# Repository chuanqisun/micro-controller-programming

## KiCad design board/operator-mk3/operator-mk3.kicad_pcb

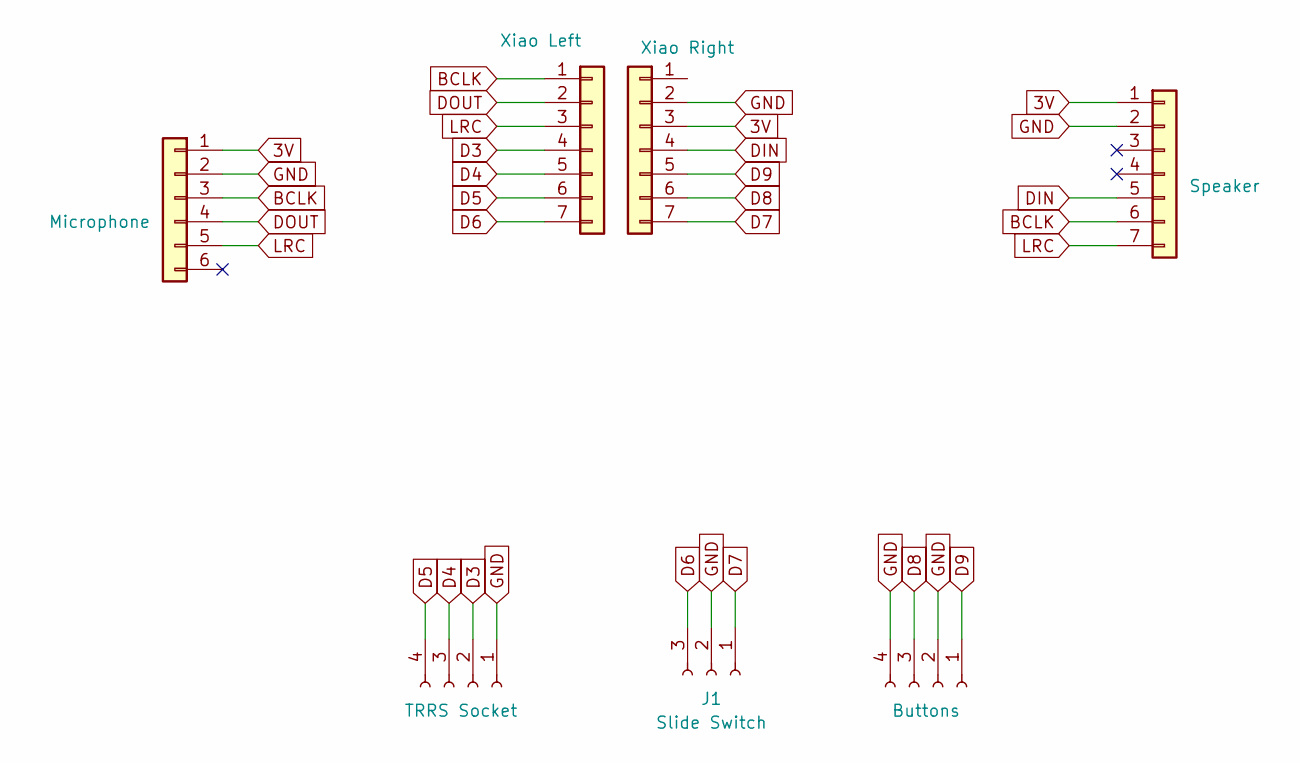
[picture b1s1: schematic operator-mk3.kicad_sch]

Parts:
J1: Slide Switch; PinSocket_1x03_P2.54mm_Vertical
J2: Microphone; PinSocket_1x06_P2.54mm_Vertical
J3: Buttons; PinSocket_1x04_P2.54mm_Vertical
J4: Speaker; PinSocket_1x07_P2.54mm_Vertical
J5: Xiao Left; PinSocket_1x07_P2.54mm_Vertical
J6: Xiao Right; PinSocket_1x07_P2.54mm_Vertical
J8: TRRS Socket; PinSocket_1x04_P2.54mm_Vertical

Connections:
3V: J2.1, J4.1, J6.3
BCLK: J2.3, J4.6, J5.1
D3: J5.4, J8.2
D4: J5.5, J8.3
D5: J5.6, J8.4
D6: J1.3, J5.7
D7: J1.1, J6.7
D8: J3.3, J6.6
D9: J3.1, J6.5
DIN: J4.5, J6.4
DOUT: J2.4, J5.2
GND: J1.2, J2.2, J3.2, J3.4, J4.2, J6.2, J8.1
LRC: J2.5, J4.7, J5.3

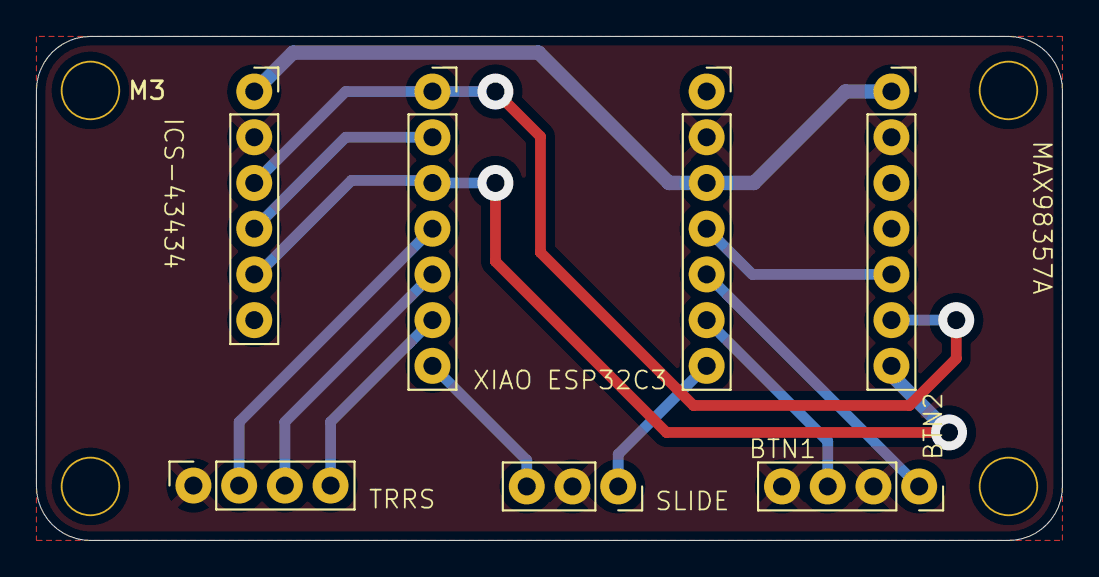
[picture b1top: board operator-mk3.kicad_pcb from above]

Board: 2 copper layers, 57.0 x 28.0 mm, 7 parts (0 on the bottom side), 13 nets.

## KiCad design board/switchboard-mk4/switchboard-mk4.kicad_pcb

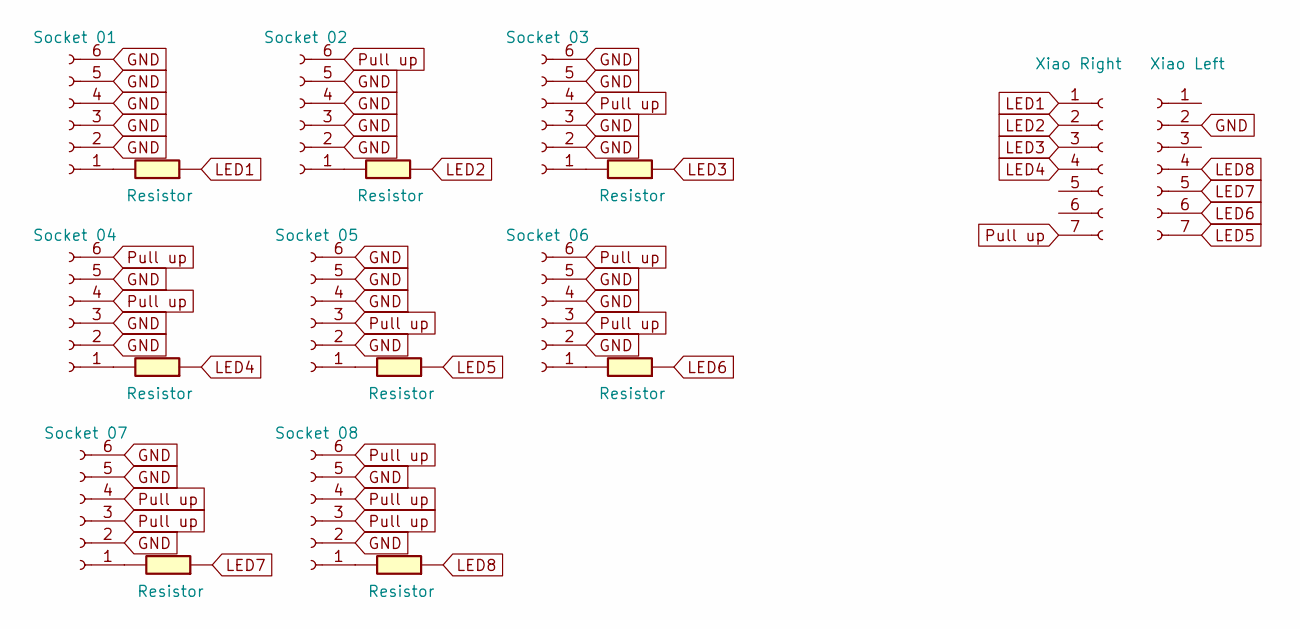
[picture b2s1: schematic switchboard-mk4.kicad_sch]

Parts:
J1: Socket 02; PinSocket_1x06_P2.54mm_Vertical
J2: Socket 03; PinSocket_1x06_P2.54mm_Vertical
J3: Socket 01; PinSocket_1x06_P2.54mm_Vertical
J4: Socket 06; PinSocket_1x06_P2.54mm_Vertical
J5: Socket 05; PinSocket_1x06_P2.54mm_Vertical
J6: Socket 04; PinSocket_1x06_P2.54mm_Vertical
J7: Socket 07; PinSocket_1x06_P2.54mm_Vertical
J8: Socket 08; PinSocket_1x06_P2.54mm_Vertical
J9: Xiao Right; PinSocket_1x07_P2.54mm_Vertical
J10: Xiao Left; PinSocket_1x07_P2.54mm_Vertical
R1, R2, R7, R8, R9, R10, R11, R12: Resistor; R_1206

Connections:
GND: J1.2, J1.3, J1.4, J1.5, J2.2, J2.3, J2.5, J2.6, J3.2, J3.3, J3.4, J3.5, J3.6, J4.2, J4.4, J4.5, J5.2, J5.4, J5.5, J5.6, J6.2, J6.3, J6.5, J7.2, J7.5, J7.6, J8.2, J8.5, J10.2
LED1: J9.1, R8.2
LED2: J9.2, R7.2
LED3: J9.3, R2.2
LED4: J9.4, R1.2
LED5: J10.7, R9.2
LED6: J10.6, R10.2
LED7: J10.5, R11.2
LED8: J10.4, R12.2
unnamed: J1.1, R7.1
unnamed: J2.1, R2.1
unnamed: J3.1, R8.1
unnamed: J4.1, R10.1
unnamed: J5.1, R9.1
unnamed: J6.1, R1.1
unnamed: J7.1, R11.1
unnamed: J8.1, R12.1
Pull up: J1.6, J2.4, J4.3, J4.6, J5.3, J6.4, J6.6, J7.3, J7.4, J8.3, J8.4, J8.6, J9.7

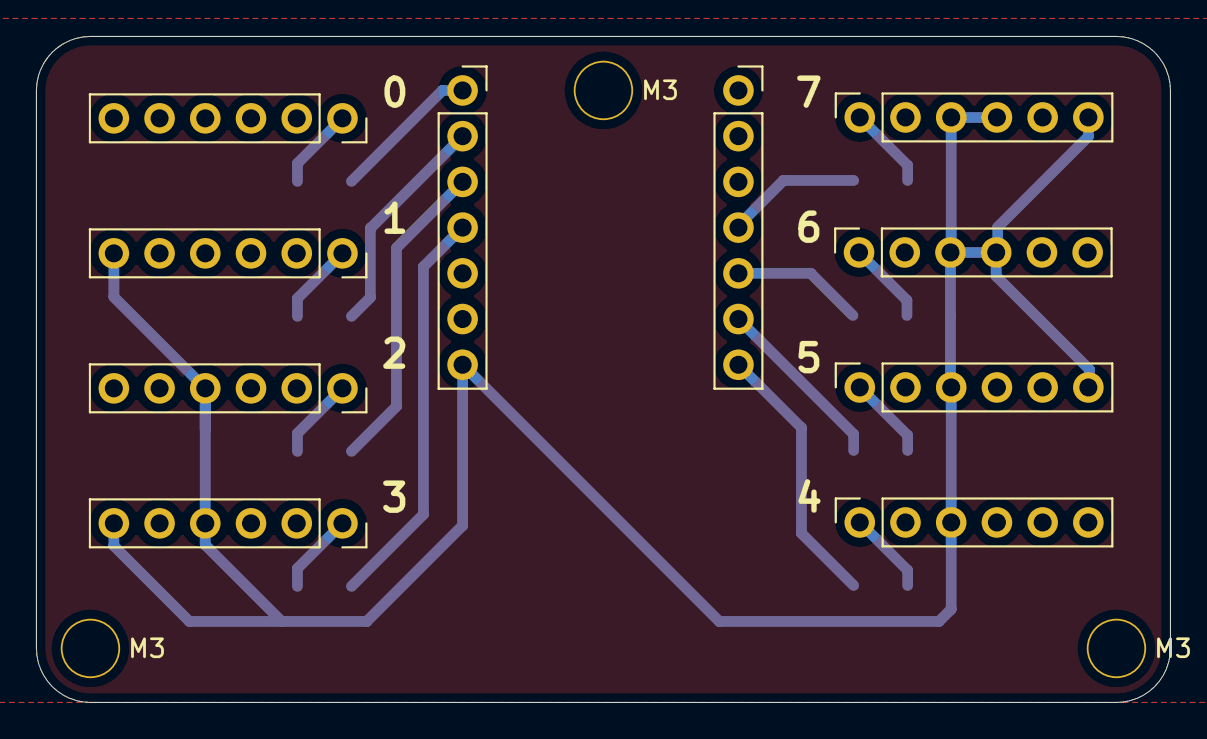
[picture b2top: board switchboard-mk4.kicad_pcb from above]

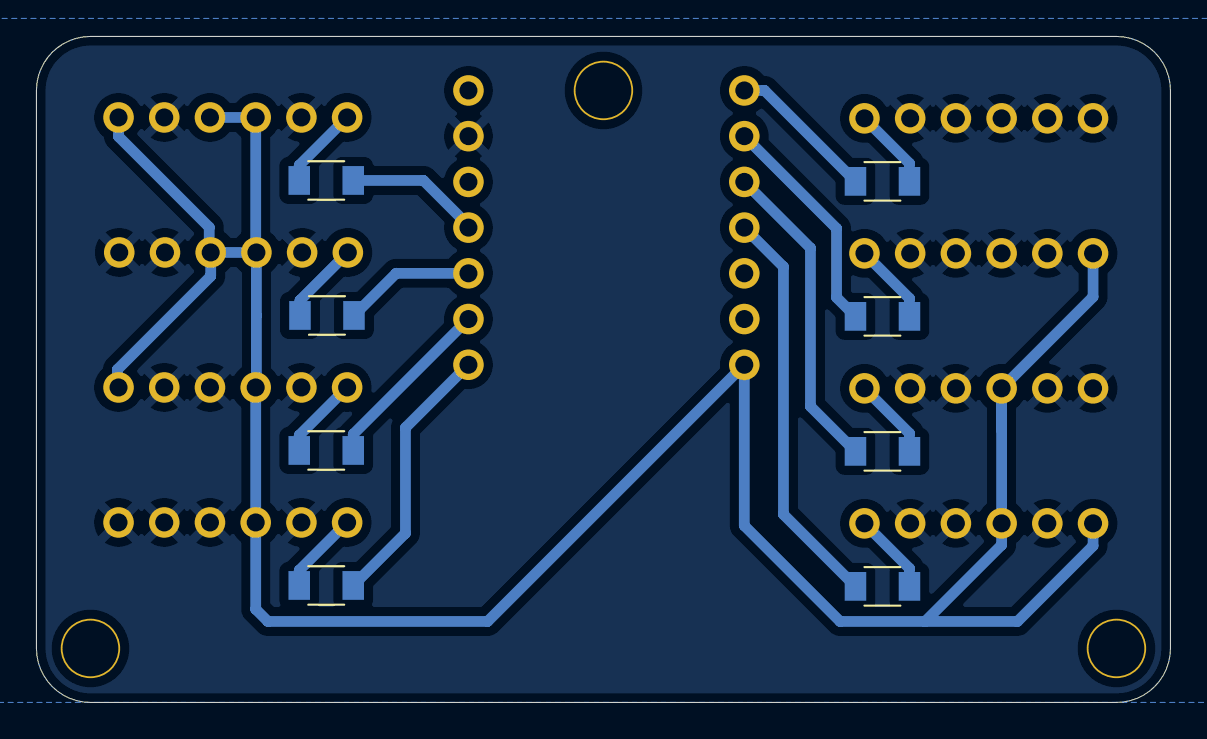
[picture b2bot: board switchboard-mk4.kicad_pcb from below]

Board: 2 copper layers, 63.0 x 37.0 mm, 18 parts (8 on the bottom side), 18 nets.

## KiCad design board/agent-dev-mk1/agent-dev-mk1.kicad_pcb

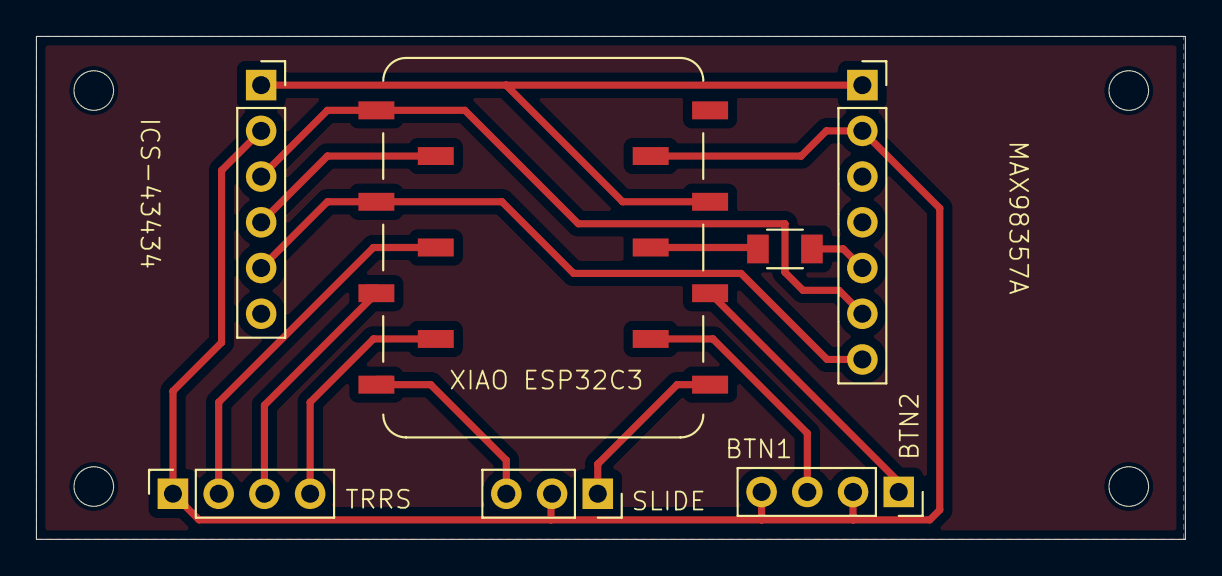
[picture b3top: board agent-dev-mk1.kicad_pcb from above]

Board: 2 copper layers, 63.8 x 27.9 mm, 7 parts (0 on the bottom side), 14 nets.

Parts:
J1: Slide Switch; PinSocket_1x03_P2.54mm_Vertical
J2: Microphone; PinSocket_1x06_P2.54mm_Vertical
J3: Buttons; PinSocket_1x04_P2.54mm_Vertical
J4: Speaker; PinSocket_1x07_P2.54mm_Vertical
J8: TRRS Socket; PinSocket_1x04_P2.54mm_Vertical
M1: XIAO ESP32; Module_XIAO_Generic_SocketSMD
R: jumper; R_1206

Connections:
3V: J2.1, J4.1, M1.12 (3V3)
BCLK: J2.3, J4.6, M1.1 (D0)
D3: J8.2, M1.4 (D3)
D4: J8.3, M1.5 (D4)
D5: J8.4, M1.6 (D5)
D6: J1.3, M1.7 (D6)
D7: J1.1, M1.8 (D7)
D8: J3.3, M1.9 (D8)
D9: J3.1, M1.10 (D9)
DIN: M1.11 (D10), R.1
DOUT: J2.4, M1.2 (D1)
GND: J1.2, J2.2, J3.2, J3.4, J4.2, J8.1, M1.13 (GND)
LRC: J2.5, J4.7, M1.3 (D2)
unnamed: J4.5, R.2

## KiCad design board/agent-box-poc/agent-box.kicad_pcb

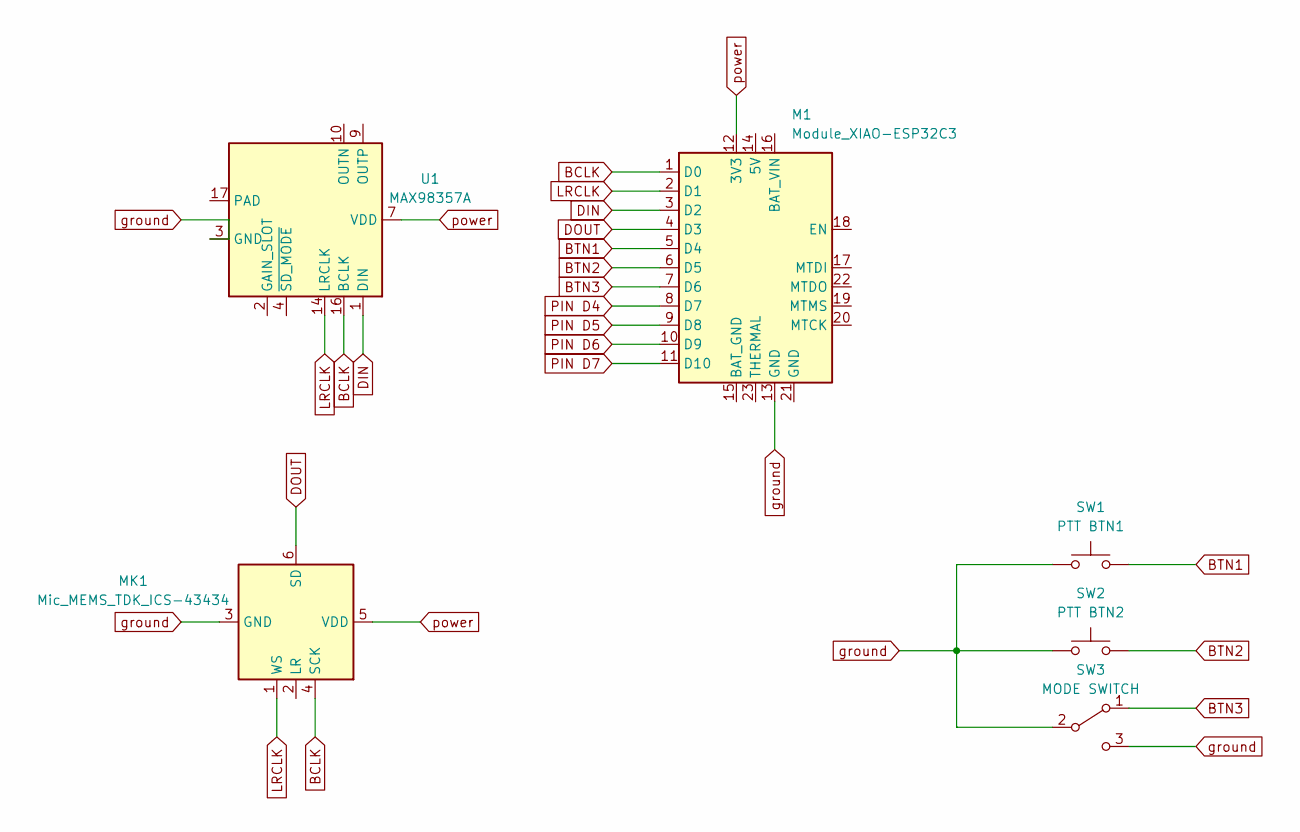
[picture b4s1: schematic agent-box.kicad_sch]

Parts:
M1: Module_XIAO-ESP32C3; SeeedStudio_XIAO_ESP32C3
MK1: Mic_MEMS_TDK_ICS-43434
SW1: PTT BTN1; Button_CnK_PTS636.0_6x3.5mm
SW2: PTT BTN2; Button_CnK_PTS636.0_6x3.5mm
SW3: MODE SWITCH; Switch_Slide_RightAngle_CnK_AYZ0102AGRLC_7.2x3mm
U1: MAX98357A; TQFN-16-1EP_3x3mm_P0.5mm_EP1.23x1.23mm

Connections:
BCLK: M1.1 (D0), MK1.4 (SCK), U1.16 (BCLK)
BTN1: M1.5 (D4), SW1.2
BTN2: M1.6 (D5), SW2.2
BTN3: M1.7 (D6), SW3.1 (A)
DIN: M1.3 (D2), U1.1 (DIN)
DOUT: M1.4 (D3), MK1.6 (SD)
LRCLK: M1.2 (D1), MK1.1 (WS), U1.14 (LRCLK)
PIN D4: M1.8 (D7); also elsewhere on the board
PIN D5: M1.9 (D8); also elsewhere on the board
PIN D6: M1.10 (D9); also elsewhere on the board
PIN D7: M1.11 (D10); also elsewhere on the board
ground: M1.13 (GND), MK1.3 (GND), SW1.1, SW2.1, SW3.2 (B), SW3.3 (C), U1.3 (GND), U1.11 (GND), U1.15 (GND)
power: M1.12 (3V3), MK1.5 (VDD), U1.7 (VDD), U1.8 (VDD)

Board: 2 copper layers, 7 parts (0 on the bottom side), 13 nets, no tracks yet.

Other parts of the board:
J1: I2S Socket; PinSocket_01x04_P2.54mm_Vertical_SMD

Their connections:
PIN D4: J1.1; also elsewhere on the board
PIN D5: J1.2; also elsewhere on the board
PIN D6: J1.3 (Pin_1); also elsewhere on the board
PIN D7: J1.4 (Pin_2); also elsewhere on the board

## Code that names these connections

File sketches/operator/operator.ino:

// Read digital inputs D3, D4, D5 and I2S microphone on D0 (BCLK), D1 (DOUT), D2 (LRC)
// Uses Arduino Audio Tools library for I2S microphone input

#include "AudioTools.h"

// Digital input pins
const int inputPins[] = { D3, D4, D5 };
const char* inputNames[] = { "D3", "D4", "D5" };
const int numInputs = 3;

// I2S configuration
I2SStream i2s;
StreamCopy copier(i2s, Serial); // Stream audio data to Serial

void setup() {
  Serial.begin(115200);
  delay(50);

  // Configure digital input pins
  for (int i = 0; i < numInputs; ++i) {
    pinMode(inputPins[i], INPUT_PULLUP);
    digitalWrite(inputPins[i], HIGH); // HIGH HIGH HIGH means unplugged
  }

  // Configure I2S input for microphone
  // D0 = BCLK, D1 = DOUT (DIN for mic), D2 = LRC (WS)
  auto config = i2s.defaultConfig(RX_MODE);
  config.pin_bck = D0;   // Bit Clock (BCLK)
  config.pin_data = D1;  // Data Out (DOUT from mic perspective, DIN for us)
  config.pin_ws = D2;    // Word Select / Left-Right Clock (LRC)
  config.sample_rate = 16000;  // 16kHz sample rate
  config.bits_per_sample = 16;
  config.channels = 1;         // Mono microphone
  config.i2s_format = I2S_STD_FORMAT;
  
  i2s.begin(config);

  Serial.println("Input monitor with I2S microphone started");
  Serial.println("I2S Config: D0=BCLK, D1=DOUT, D2=LRC, 16kHz, 16-bit, Mono");
}

void loop() {
  // Read and report digital inputs
  for (int i = 0; i < numInputs; ++i) {
    int v = digitalRead(inputPins[i]);
    Serial.print(inputNames[i]);
    Serial.print(": ");
    if (v == HIGH) {
      Serial.println("HIGH");
    } else {
      Serial.println("LOW");
    }
  }
  Serial.println(); // blank line between samples
  
  // Process I2S audio stream
  // This will continuously read from the I2S microphone
  copier.copy();
  
  delay(50);
}

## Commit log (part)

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2025-10-16 update notes
2025-10-17 update learning notes
2025-10-19 update pics
2025-10-22 add printer
2025-10-25 add i2s sound input
2025-10-25 reorg project
2025-10-25 update examples
2025-10-25 udp streaming
2025-10-25 add udp example
2025-10-27 add talkie demo
2025-10-27 refactor code
2025-10-27 add audio mk2
2025-10-27 audio board mk2
2025-10-27 save
2025-10-27 format notes
2025-10-27 implement realtime api
2025-10-27 add project files
2025-10-28 rename function
2025-10-28 fix code examples
2025-10-30 forking project
2025-10-30 migrate
2025-10-30 update demos
2025-10-30 add notes about the setup
2025-10-30 adjust params
2025-10-30 update note
2025-10-30 implement the server
2025-10-31 add streaming
2025-10-31 multi turn
2025-10-31 migrate folder
2025-10-31 add mp3 streaming
2025-10-31 update streaming
2025-10-31 format
2025-10-31 add sound player
2025-10-31 add package streaming flow control
2025-10-31 update server sound sreaming
2025-10-31 add 11labs
2025-10-31 streaming
2025-10-31 sound effect streaming
2025-10-31 update board
2025-10-31 integrate all server features
2025-10-31 refactor
2025-10-31 consolidate temp file path
2025-10-31 update server code
2025-11-03 working encoder
2025-11-03 archive
2025-11-03 ode to joy
2025-11-03 fix notes
2025-11-03 fix song
2025-11-03 e2e demo
2025-11-03 two sided play
2025-11-03 update draft
2025-11-03 add media
2025-11-03 add backup media
2025-11-03 add test model
2025-11-03 add progress
2025-11-03 fix bug
2025-11-03 update server
2025-11-03 fix up
2025-11-03 update prompt
2025-11-06 fork operator mk3
2025-11-06 add notes
2025-11-08 add tools bits
2025-11-08 add work archive
2025-11-09 week 10
2025-11-09 add raw notes
2025-11-09 update final image
2025-11-09 backups
2025-11-10 update outline
2025-11-10 update notes and media
2025-11-10 update docs
2025-11-10 update links
2025-11-13 scrub password
2025-11-13 add env
2025-11-13 update api doc
2025-11-13 fix api endpoint
2025-11-13 show ip by default
2025-11-13 update ui
2025-11-13 reduce machine readable data
2025-11-14 add backup
2025-11-14 add pseudocode
2025-11-14 update architecture
2025-11-14 add ip discovery logic
2025-11-15 migrate notes
2025-11-15 add servo code
2025-11-15 update ref implementation
2025-11-16 update poc
2025-11-16 update the controller for 20 servos
2025-11-16 update testing UI
2025-11-16 update test code
2025-11-16 update test
2025-11-16 add latency measure
2025-11-16 add testing note
2025-11-16 add performance notes
2025-11-16 update test note
2025-11-16 archive tests
2025-11-16 add bluetooth test video
2025-11-16 add screenshot
2025-11-17 update blog notes
2025-11-22 update week 12 progress
2025-11-22 add compressions script
2025-11-22 update media
2025-11-22 update sketch for switchboard mk4
2025-11-22 simple blink
2025-11-22 add led pulse test
2025-11-24 add new board design
2025-11-24 add led bluetooth test
2025-11-24 add week 12 skeleton code
2025-11-24 rename files
2025-11-24 add led mapping
2025-11-24 increase timeout
2025-11-24 update device name
2025-11-24 shorten bluetooth name
2025-11-24 implement full game
2025-11-24 add score card
2025-11-24 add api key for remote messaging
2025-11-25 add video
2025-11-25 add videos
2025-11-25 add raw photos
2025-11-25 add raw videos
2025-11-25 add vieo
2025-11-26 fix video
2025-11-28 add throughput test (failed)
2025-11-29 add server
2025-11-29 gather source code for week13
2025-11-29 auto configure ip
2025-11-29 update network info for testing
2025-11-29 safely store wifi password
2025-11-29 add testing notes
2025-11-29 create http server
2025-11-29 reading ip
2025-11-29 ip discovery
2025-11-29 bluetooth connection
2025-11-29 use standard message format
2025-11-29 renaming
2025-11-29 fix script
2025-11-29 only send probe when changed
2025-11-29 add probe api
2025-11-29 add cancellation
2025-11-29 update data flow
2025-11-30 find operator address after BLE
2025-11-30 simplify handshake
2025-11-30 expose sender ip api
2025-11-30 full hand shake
2025-11-30 update operator address
2025-11-30 remove dead code
2025-11-30 add switchboard
2025-11-30 implement sse
2025-11-30 add manual speek
2025-11-30 programmatic speak
2025-11-30 update todo
2025-12-01 remove debug
2025-12-01 add sound test
2025-12-01 add server v2
2025-12-01 add server infra
2025-12-01 banch version
2025-12-01 connect and blink
2025-12-01 ui driven connection
2025-12-01 connection flow
2025-12-01 handle timeout
2025-12-01 add timeout for connection
2025-12-01 add operator connection
2025-12-01 connect and disconnect
2025-12-01 update probe number
2025-12-01 gather operator address
2025-12-01 rename
2025-12-01 add speaker
2025-12-01 add simulation
2025-12-01 fix connection handshake
2025-12-01 state refactor
2025-12-01 add ai connection management
2025-12-01 pretty print json
2025-12-02 implement DPU server
2025-12-02 prepare voice integration
2025-12-02 propagate button state
2025-12-02 update schematic
2025-12-02 update screenshots
2025-12-02 update button
2025-12-02 add button state machine
2025-12-02 prototype audio
2025-12-02 configure realtime
2025-12-02 fix speech
2025-12-02 add test files
2025-12-02 add debugging playback
2025-12-02 add playback debugger
2025-12-02 increase frequency
2025-12-02 add critical buffer drain
2025-12-02 remove unused parameters
2025-12-02 refactor silence detection
2025-12-02 remove throttling
2025-12-02 skip empty buffer
2025-12-02 add audio debugger
2025-12-02 add gemini comparison
2025-12-03 clean up old code
2025-12-03 disable gemini faeures
2025-12-03 handle story display
2025-12-03 update game play
2025-12-03 implement gameplay
2025-12-03 switch to openai for consistent output
2025-12-03 update game
2025-12-03 fading light
2025-12-03 adjust fade timer
2025-12-03 relax timeout
2025-12-03 add ideas
2025-12-05 add trace notes
2025-12-05 migrate week13 work
2025-12-05 rename file
2025-12-05 remove throttle
2025-12-05 stream audio to device
2025-12-05 update calibration
2025-12-05 add bamboo models
2025-12-05 add prusa file
2025-12-06 update ntoes and records
2025-12-07 add week14 design assets
2025-12-07 update final notes
2025-12-07 white space change
2025-12-08 organize files
2025-12-10 update print
2025-12-10 handle mock probing
2025-12-10 update button mock
2025-12-10 add microphone output dump
2025-12-10 add duplex test
2025-12-10 update test file
2025-12-10 add comment
2025-12-10 add reference imp
2025-12-11 add demos
2025-12-11 fix streaming
2025-12-11 enable mutex transmission
2025-12-11 fix the sender rate
2025-12-11 add reference implementation
2025-12-11 text only mode, finally working
2025-12-11 switch to audio model
2025-12-11 remove debug sound
2025-12-11 refactor to gemini
2025-12-11 add streaming debugger
2025-12-11 add stream debugger
2025-12-11 fix streaming issue
2025-12-11 update thinking config
2025-12-11 unify model
2025-12-11 add openai equivalent
2025-12-11 unifying buffers
2025-12-11 add openai agent sdk
2025-12-11 handle interruption
2025-12-11 update adventure
2025-12-11 add game engine
2025-12-11 main game loop
2025-12-11 e2e gameplay flow
2025-12-12 fix blinking mode
2025-12-12 implement positional blinking
2025-12-12 update games
2025-12-12 update game logic
2025-12-12 update game play script
2025-12-12 update init
2025-12-12 immersive setup
2025-12-12 reduce wait
2025-12-12 more aggresive cancellation
2025-12-12 whitespace
2025-12-12 prompt fix
2025-12-12 update week 15
2025-12-13 update finales note
2025-12-13 add unit 2
2025-12-13 use unit 1
2025-12-13 multi-device refactor
2025-12-13 remove blocking LED control
2025-12-13 update game design docs
2025-12-13 update game play scripts
2025-12-13 dead code removal
2025-12-13 update characters
2025-12-13 update character selection
2025-12-13 add voice actor
2025-12-14 intrinsic role play
2025-12-14 update audio reset
2025-12-14 add debugger
2025-12-14 deterministic character setup
2025-12-14 reduce token budget
2025-12-14 audio compression for udp
2025-12-14 fix pcm rate mismatch
2025-12-14 revert rate control
2025-12-14 update gemini live
2025-12-14 implement azure transcription
2025-12-14 prepare for game v2
2025-12-14 migrate to openai
2025-12-14 migrate all
2025-12-14 archive code
2025-12-14 clean up
2025-12-14 update transcript logic
2025-12-14 expose led state
2025-12-14 white space
2025-12-14 render button state on the UI
2025-12-14 add context prompt refactor
2025-12-14 light status
2025-12-14 update controller
2025-12-14 handle app reset
2025-12-14 simplify UI
2025-12-14 update voice
2025-12-14 reomve deadcode
2025-12-14 remove unused
2025-12-14 fix server reload
2025-12-14 connect laptop audio
2025-12-14 add audio control
2025-12-14 add audo stream
2025-12-14 add single plyaer UI
2025-12-15 switch player
2025-12-15 update rules
2025-12-15 multi-player registration
2025-12-15 add easter egg
2025-12-15 add intro
2025-12-15 add dice
2025-12-15 dice mode
2025-12-15 adjust prompt
2025-12-15 add large media
2025-12-15 add rest of videos
2025-12-15 update QR
2025-12-15 remove diagnostic height limit
2025-12-15 adjust buffer
2025-12-15 add music
2025-12-15 auto clear log
2025-12-15 enlarge videos
2025-12-16 add prusa config
2025-12-16 fix env
2025-12-16 add final app code
2025-12-17 refactor prompt
2025-12-17 remove unused docs
2025-12-17 fix typo
2025-12-18 remove unused deps
